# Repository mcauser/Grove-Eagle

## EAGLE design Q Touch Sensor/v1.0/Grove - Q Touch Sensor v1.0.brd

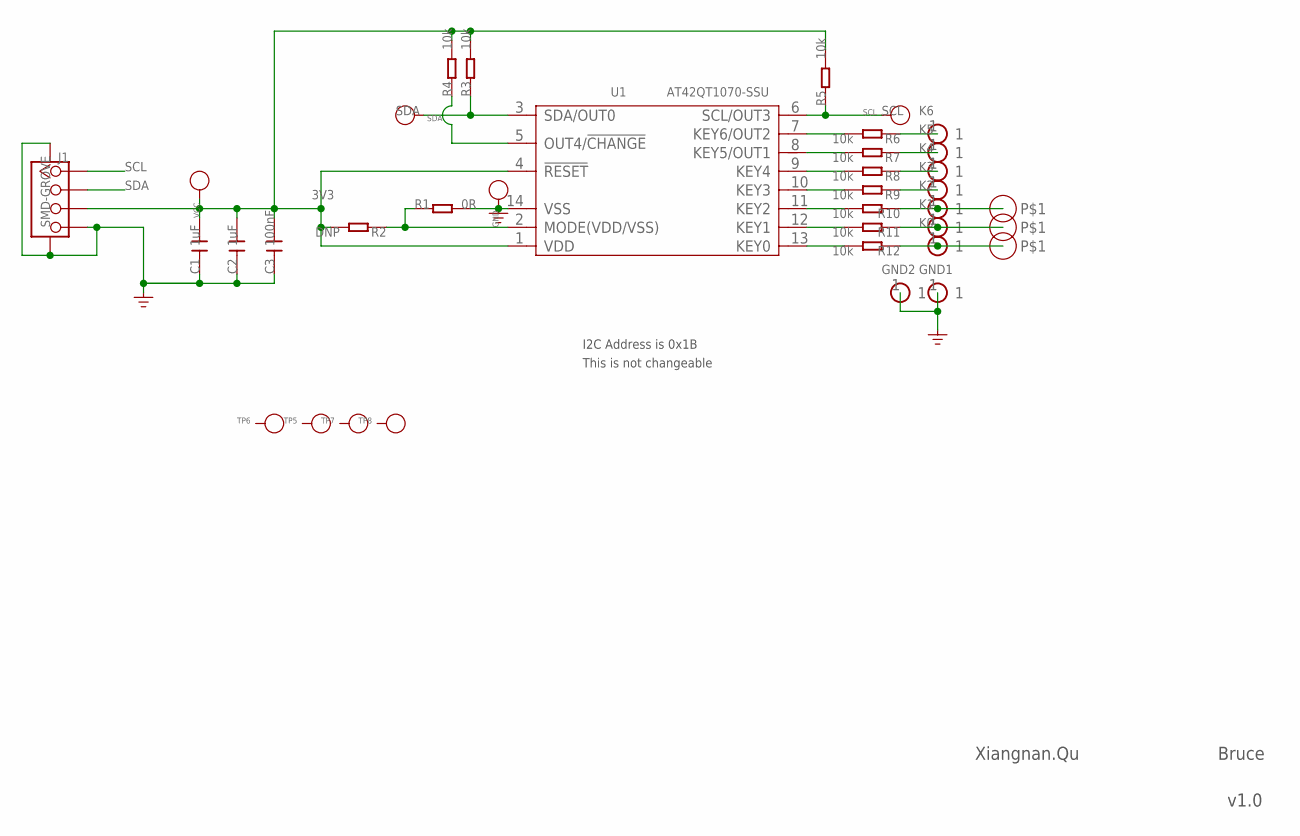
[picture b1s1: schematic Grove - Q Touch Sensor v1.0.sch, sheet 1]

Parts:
C1, C2: 1uF; C0603
C3: 100nF; C0603
GND: PAD-TEST-POINT'4545'; TP_4545
GND1, GND2: HEADER-1P-35; 1P-65/35MIL
J1: SMD-GROVE; 4P-SMD-2.0
K0, K1, K2, K3, K4, K5, K6: HEADER-1P-35; 1P-65/35MIL
P1, P2, P3: PAD-HOLE; 1P-D6MM
R1: 0R; R0603
R2: DNP; R0603
R3, R4, R5, R6, R7, R8, R9, R10, R11, R12: 10k; R0603
SCL: PAD-TEST-POINT'4545'; TP_4545
SDA: PAD-TEST-POINT'4545'; TP_4545
TP5, TP6, TP7, TP8: PAD-TEST-POINT'4545'; TP_4545
U1: AT42QT1070-SSU; SOIC14
VCC: PAD-TEST-POINT'4545'; TP_4545

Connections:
3V3: C1.2, C2.2, C3.2, J1.3, R2.2, R3.2, R4.2, R5.2, U1.1 (VDD), U1.4 (!RESET), VCC.T
GND: C1.1, C2.1, C3.1, GND.T, GND1.1, GND2.1, J1.4, J1.SS1, J1.SS2, R1.2, U1.14 (VSS)
unnamed: R1.1, R2.1, U1.2 (MODE(VDD/VSS))
unnamed: R6.2, U1.7 (KEY6/OUT2)
unnamed: K6.1, R6.1
unnamed: R7.2, U1.8 (KEY5/OUT1)
unnamed: R8.2, U1.9 (KEY4)
unnamed: R9.2, U1.10 (KEY3)
unnamed: R10.2, U1.11 (KEY2)
unnamed: R11.2, U1.12 (KEY1)
unnamed: R12.2, U1.13 (KEY0)
unnamed: R4.1, U1.5 (OUT4/!CHANGE)
unnamed: K5.1, R7.1
unnamed: K4.1, R8.1
unnamed: K3.1, R9.1
unnamed: K2.1, P1.1, R10.1
unnamed: K1.1, P2.1, R11.1
unnamed: K0.1, P3.1, R12.1
SCL: J1.1, R5.1, SCL.T, U1.6 (SCL/OUT3)
SDA: J1.2, R3.1, SDA.T, U1.3 (SDA/OUT0)

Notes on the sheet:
Xiangnan.Qu
Bruce
v1.0
I2C Address is 0x1B
This is not changeable

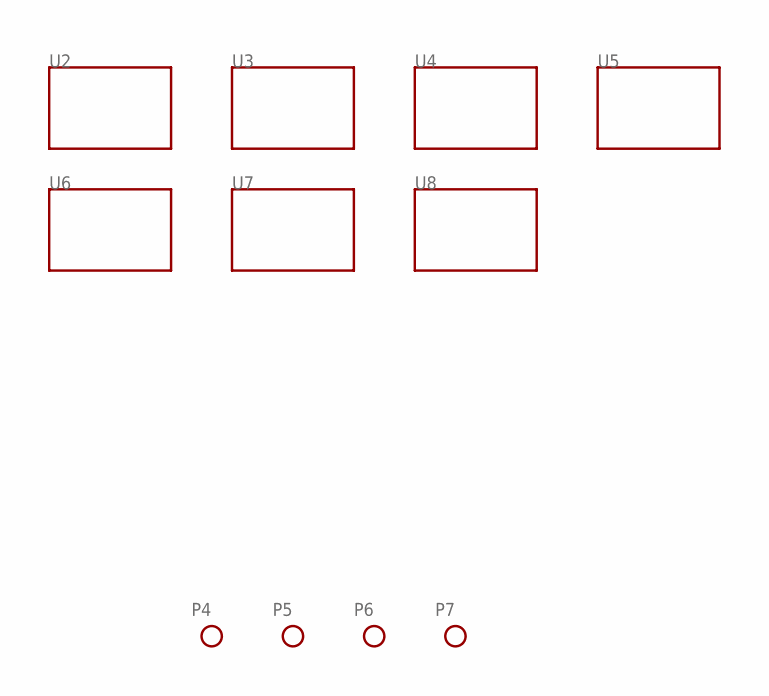
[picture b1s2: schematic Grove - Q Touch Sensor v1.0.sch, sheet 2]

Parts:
P4, P5, P6, P7: PAD-MARK; ROUND-MARK-1.0
U2, U3, U4, U5, U6, U7, U8: TWIG'2U'; GROVE-TEST-PLATFORM

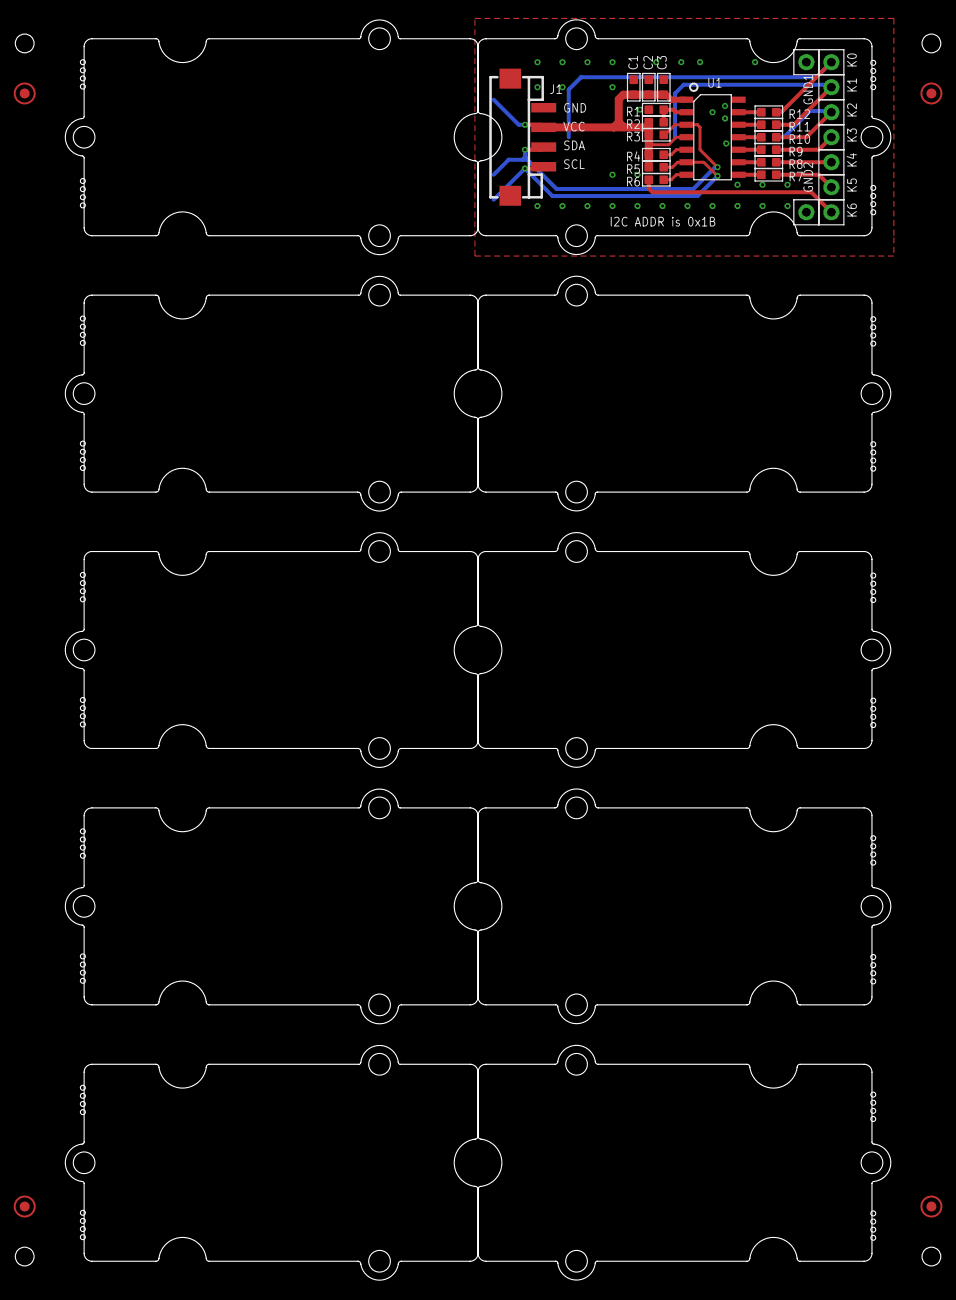
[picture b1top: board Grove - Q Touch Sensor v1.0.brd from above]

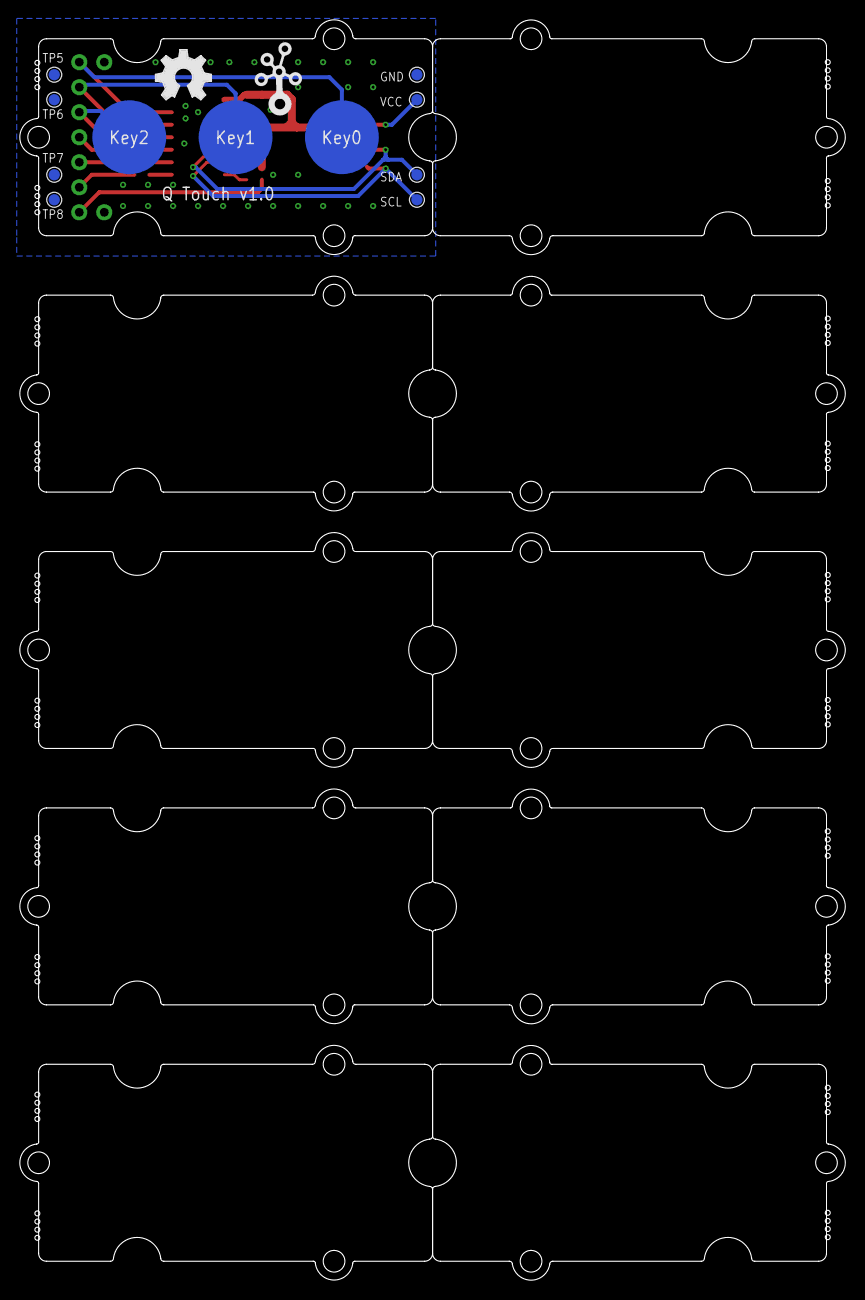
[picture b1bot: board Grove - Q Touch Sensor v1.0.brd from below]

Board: 2 copper layers, 83.8 x 128.0 mm, 53 parts (13 on the bottom side), 20 nets.

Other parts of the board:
U10, U11: GROVE-TEST-PLATFORM
U$5: GROVE-2CONNECTOR-SMD
U$6: OSHW_FILLX200_NOTEXT
U$7: TWIGLOGO

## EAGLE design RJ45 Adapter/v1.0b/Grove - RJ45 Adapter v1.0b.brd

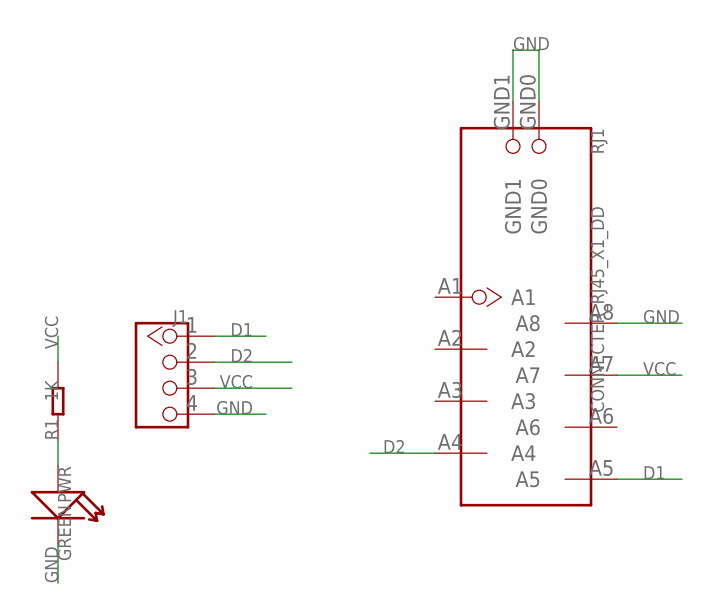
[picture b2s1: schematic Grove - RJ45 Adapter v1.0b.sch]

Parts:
J1: TWIG-4P-2.0-2.0; 4P-2.0
PWR: GREEN; LED-0603
R1: 1K; R0603
RJ1: CONNECTER_RJ45_X1_DD; CONNECTER_RJ45_X1

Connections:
D1: J1.1, RJ1.A5
D2: J1.2, RJ1.A4
GND: J1.4, PWR.-, RJ1.A8, RJ1.GND0, RJ1.GND1
unnamed: PWR.+, R1.1
VCC: J1.3, R1.2, RJ1.A7

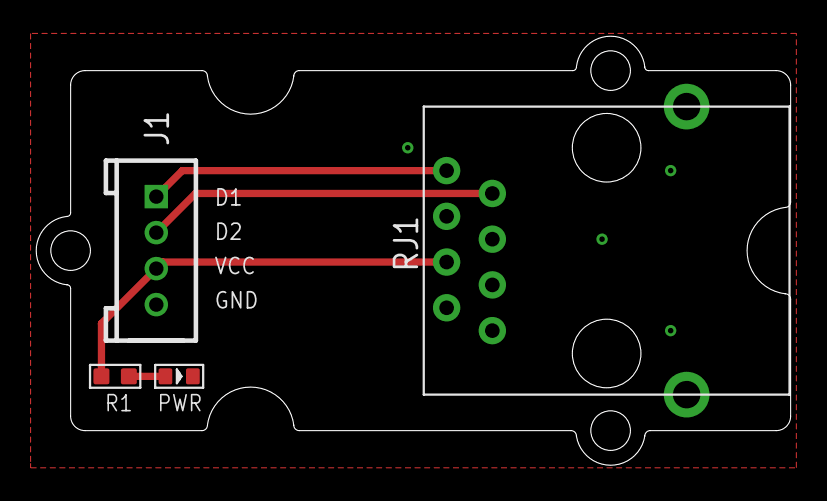
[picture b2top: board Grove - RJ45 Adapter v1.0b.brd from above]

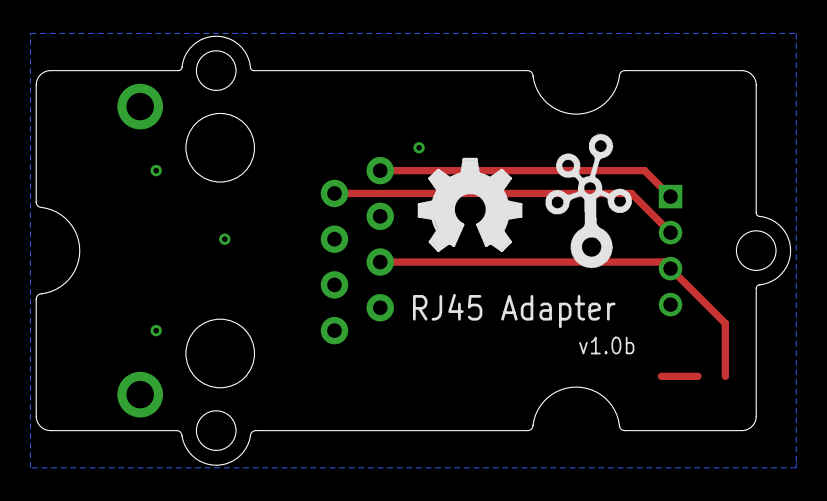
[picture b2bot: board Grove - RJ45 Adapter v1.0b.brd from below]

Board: 2 copper layers, 41.9 x 23.8 mm, 7 parts (2 on the bottom side), 5 nets.

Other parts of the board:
U$1: 2U-DIM-W/DRILL
U$2: OSHW_FILLX200_NOTEXT
U$3: TWIGLOGO

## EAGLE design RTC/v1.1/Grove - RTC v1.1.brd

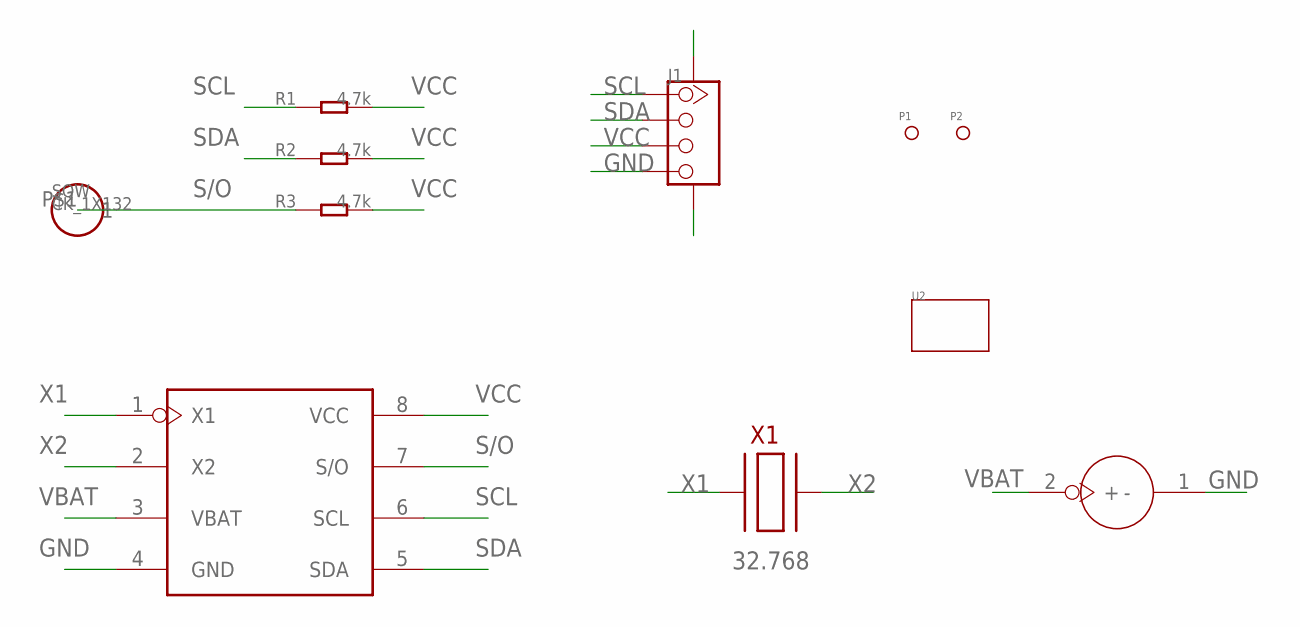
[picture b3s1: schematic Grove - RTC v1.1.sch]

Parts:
J1: TWIG-4P-2.0-SMD-FEMALE-REINFORCE'DD'; 4P-SMD-2.0
P1, P2: PAD-MARK; ROUND-MARK-1.0
R1, R2, R3: 4.7k; 0603
SQW: CK_1X132; CK_1X1
U1: DS1307; SO08
U2: TWIG-2U; 2U-DIM-W/-DRILL
U3: BATTERYBATTERY1225_SMT; BATTERY1225_SMT
X1: XTL_S

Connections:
GND: J1.4, J1.SS1, J1.SS2, U1.4 (GND), U3.1 (-)
S/O: R3.1, SQW.P$1, U1.7 (S/O)
SCL: J1.1, R1.1, U1.6 (SCL)
SDA: J1.2, R2.1, U1.5 (SDA)
VBAT: U1.3 (VBAT), U3.2 (+)
VCC: J1.3, R1.2, R2.2, R3.2, U1.8 (VCC)
X1: U1.1 (X1), X1.1
X2: U1.2 (X2), X1.2

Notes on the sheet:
32.768

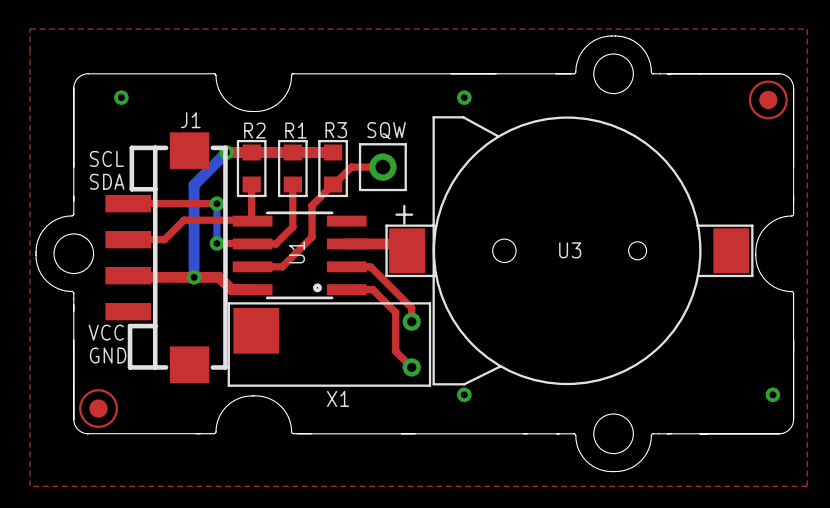
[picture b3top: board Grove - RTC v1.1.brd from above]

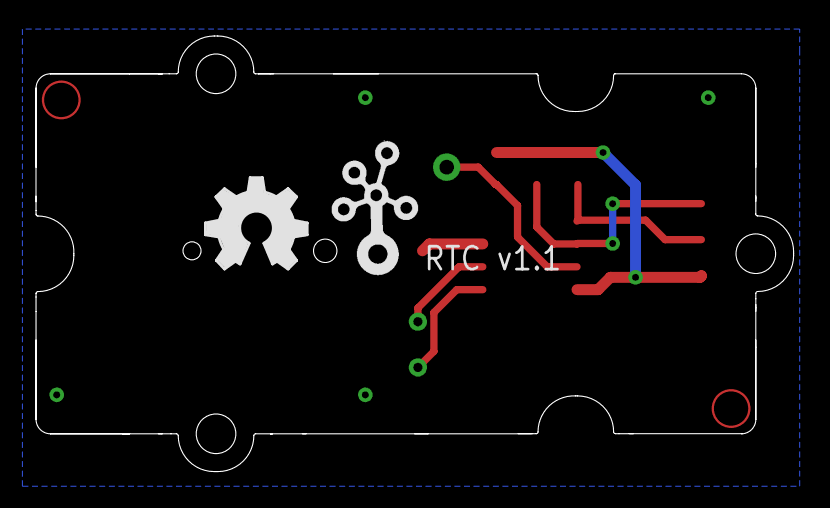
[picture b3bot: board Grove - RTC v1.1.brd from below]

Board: 2 copper layers, 42.1 x 24.2 mm, 13 parts (2 on the bottom side), 8 nets.

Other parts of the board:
U$1: OSHW_FILLX200_NOTEXT
U$3: TWIGLOGO

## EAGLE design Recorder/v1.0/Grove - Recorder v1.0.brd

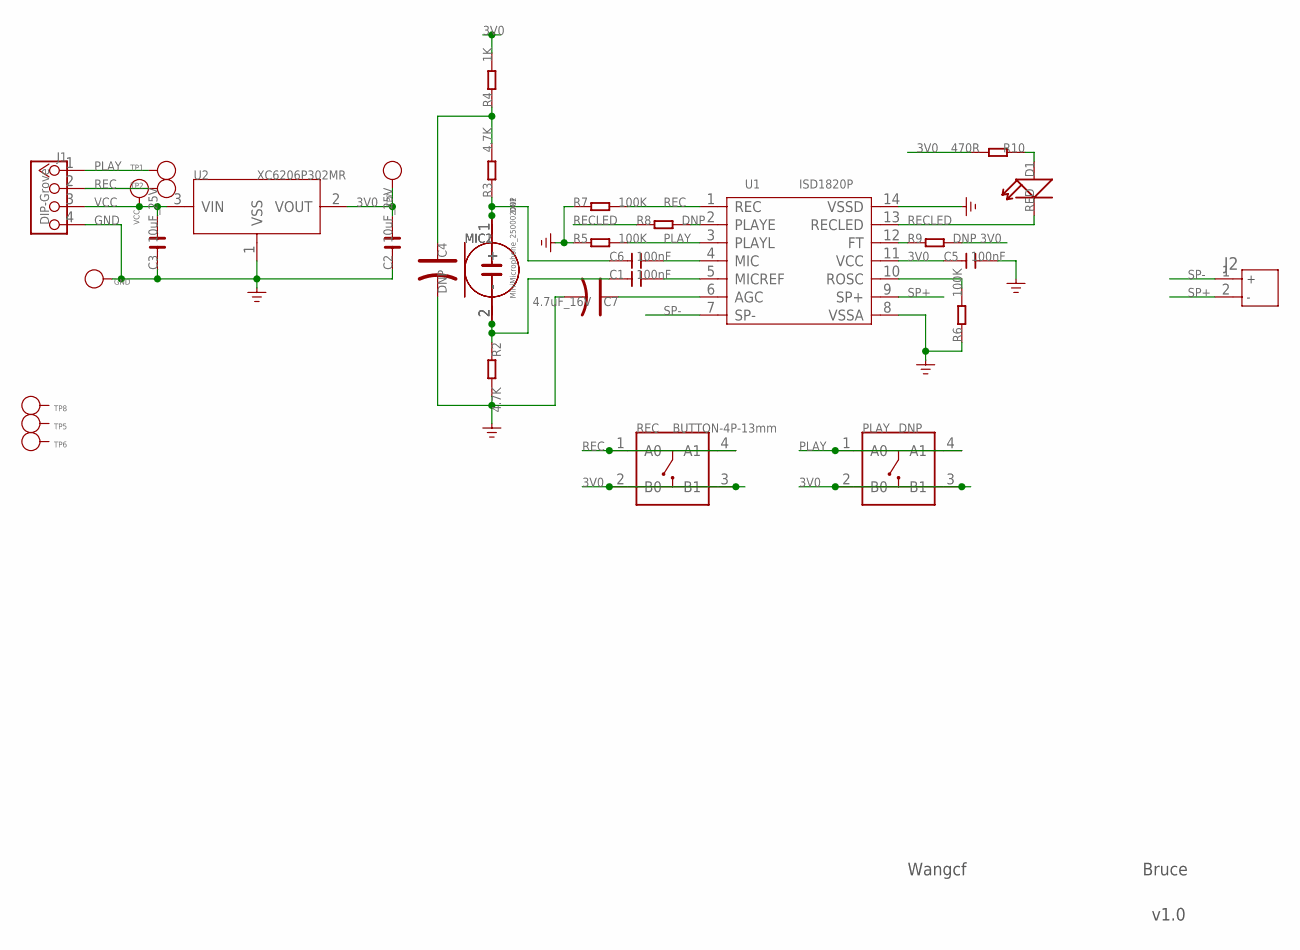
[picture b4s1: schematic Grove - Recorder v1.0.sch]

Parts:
C1, C5, C6: 100nF; C0603
C2, C3: 10uF_25V; C0805
C4: DNP; AVX-A
C7: 4.7uF_16V; AVX-A
D1: RED; LED-SIDE-VIEW-0603-RIGHT
GND: PAD-TEST-POINT'4545'; TP_4545
J1: DIP-Grove; 4P-2.0
J2: JACK-JST-2P-PW'2.0'; JST-2.0
MIC1: MiniMicrophone_250002001; 2P-D8.9MM
MIC2: DNP; 2P-D8.9MM
PLAY: DNP; 4P-6.0X6.0X5.0H
R2, R3: 4.7K; R0603
R4: 1K; R0603
R5, R6, R7: 100K; R0603
R8, R9: DNP; R0603
R10: 470R; R0603
REC: BUTTON-4P-13mm; 4P-6.0X6.0X5.0H
TP1, TP2, TP5, TP6, TP7, TP8: PAD-TEST-POINT'4545'; TP_4545
U1: ISD1820P; DIP14
U2: XC6206P302MR; SOT23
VCC: PAD-TEST-POINT'4545'; TP_4545

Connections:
3V0: C2.2, C5.1, PLAY.2 (B0), PLAY.3 (B1), R4.2, R9.2, R10.2, REC.2 (B0), REC.3 (B1), TP7.T, U1.11 (VCC), U2.2 (VOUT)
GND: C2.1, C3.1, C4.-, C5.2, C7.- (2), GND.T, J1.4, R2.2, R5.1, R6.1, R7.1, U1.8 (VSSA), U1.14 (VSSD), U2.1 (VSS)
unnamed: R8.2, U1.2 (PLAYE)
unnamed: D1.1 (+), R10.1
unnamed: C7.+ (1), U1.6 (AGC)
unnamed: C1.2, U1.5 (MICREF)
unnamed: C6.2, U1.4 (MIC)
unnamed: R9.1, U1.12 (FT)
unnamed: R6.2, U1.10 (ROSC)
unnamed: C4.+, R3.2, R4.1
unnamed: C6.1, MIC1.1 (+), MIC2.1 (+), R3.1
unnamed: C1.1, MIC1.2 (-), MIC2.2 (-), R2.1
PLAY: J1.1, PLAY.1 (A0), PLAY.4 (A1), R5.2, TP1.T, U1.3 (PLAYL)
REC: J1.2, R7.2, REC.1 (A0), REC.4 (A1), TP2.T, U1.1 (REC)
RECLED: D1.2 (-), R8.1, U1.13 (RECLED)
SP+: J2.2, U1.9 (SP+)
SP-: J2.1, U1.7 (SP-)
VCC: C3.2, J1.3, U2.3 (VIN), VCC.T

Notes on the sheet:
Wangcf
Bruce
v1.0

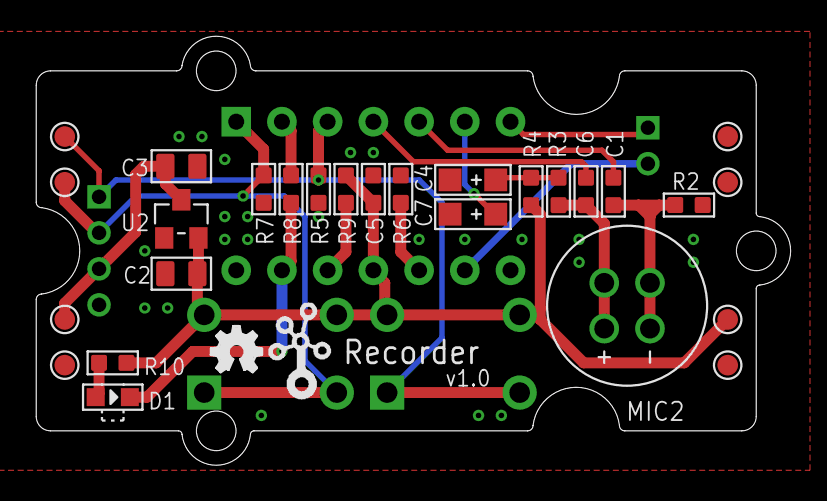
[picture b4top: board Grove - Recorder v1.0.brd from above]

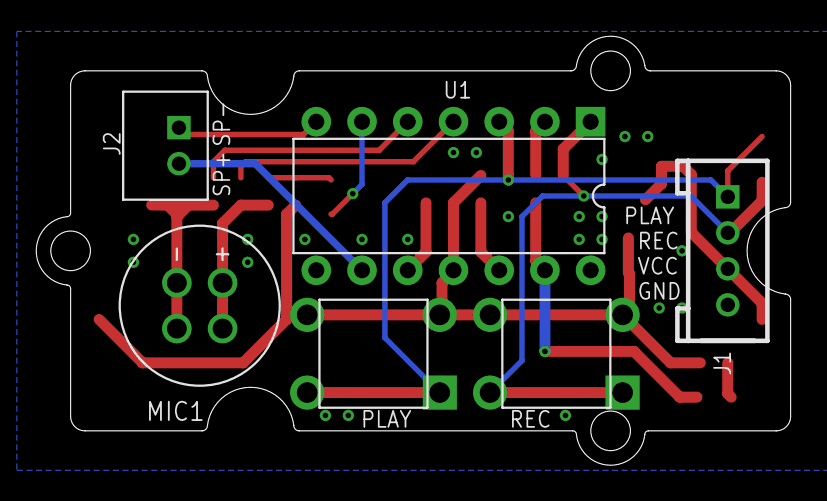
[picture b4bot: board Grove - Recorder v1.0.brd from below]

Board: 2 copper layers, 41.9 x 23.8 mm, 36 parts (6 on the bottom side), 18 nets.

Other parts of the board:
U$9: GROVE-2CONNECTOR
U$10: TWIGLOGO_SMALL
U$11: OSHW_FILLX100_NOTEXT

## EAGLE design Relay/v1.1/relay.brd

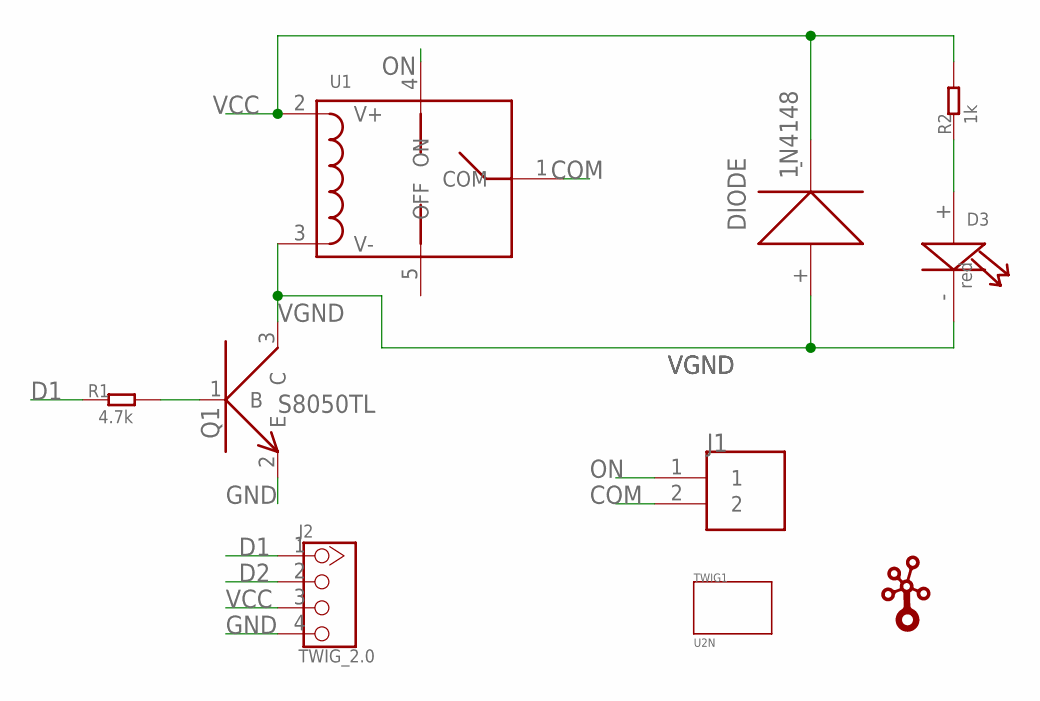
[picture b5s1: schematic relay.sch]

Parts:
D3: red; LED0805
DIODE: 1N4148; DIODE1206
J1: CON2
J2: TWIG_2.0; 2.0_1X4
Q1: NPN_9013; SOT23
R1: 4.7k; 0603
R2: 1k; 0603
TWIG1: U2N
U1: RELAY
U$1: TWIGLOGOTWIGLOGO_SMALL; TWIGLOGO_SMALL

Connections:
COM: J1.2, U1.1 (COM)
D1: J2.1, R1.1
D2: J2.2
GND: J2.4, Q1.2 (E)
unnamed: D3.+, R2.1
unnamed: Q1.1 (B), R1.2
ON: J1.1, U1.4 (ON)
VCC: DIODE.-, J2.3, R2.2, U1.2 (V+)
VGND: D3.-, DIODE.+, Q1.3 (C), U1.3 (V-)

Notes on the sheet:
S8050TL

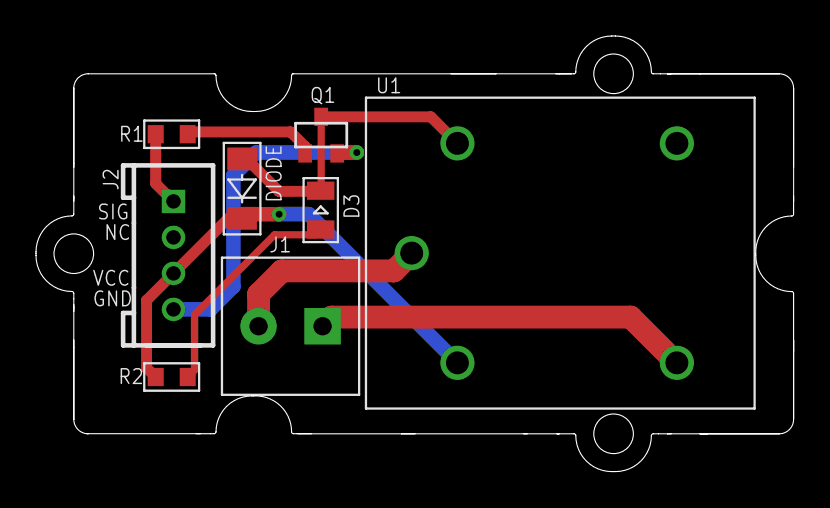
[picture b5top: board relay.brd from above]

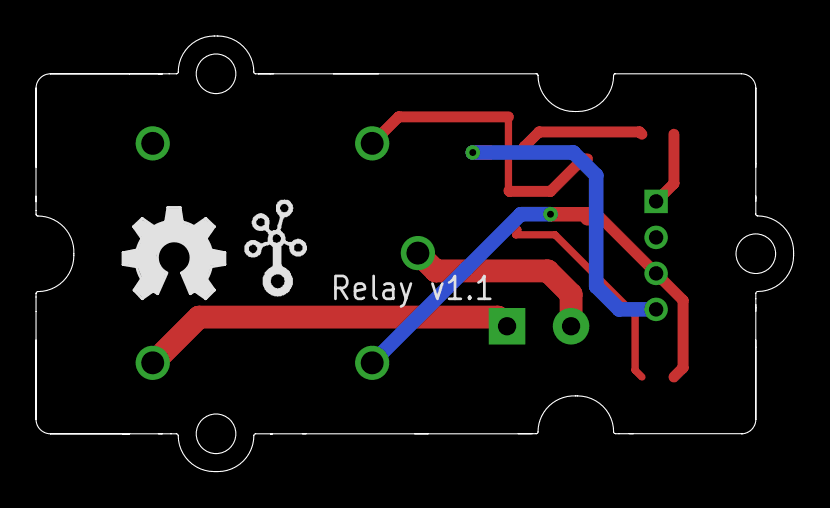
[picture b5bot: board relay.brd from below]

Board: 2 copper layers, 42.1 x 24.2 mm, 11 parts (2 on the bottom side), 8 nets.

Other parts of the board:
U$2: OSHW_FILLX200_NOTEXT

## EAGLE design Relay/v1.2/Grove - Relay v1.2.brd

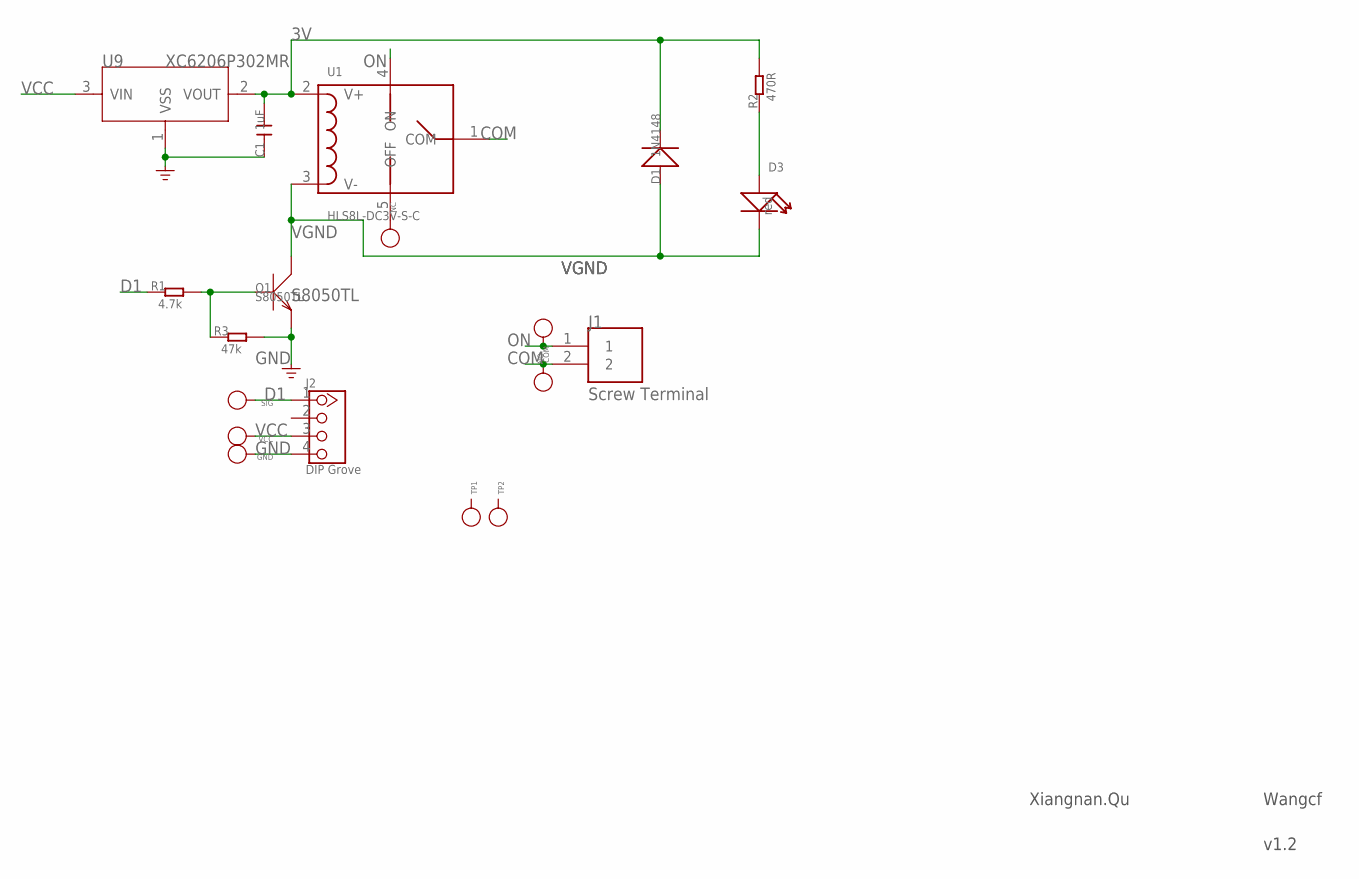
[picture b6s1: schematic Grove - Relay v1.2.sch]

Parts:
C1: 1uF; C0603
COM: PAD-TEST-POINT'4545'; TP_4545
D1: 1N4148; LL-34
D3: red; LED-0603
GND: PAD-TEST-POINT'4545'; TP_4545
J1: Screw Terminal; CON2
J2: DIP Grove; 2.0_1X4
NC: PAD-TEST-POINT'4545'; TP_4545
NO: PAD-TEST-POINT'4545'; TP_4545
Q1: S8050TL; SOT23
R1: 4.7k; R0603
R2: 470R; R0603
R3: 47k; R0603
SIG: PAD-TEST-POINT'4545'; TP_4545
TP1, TP2: PAD-TEST-POINT'4545'; TP_4545
U1: HLS8L-DC3V-S-C; RELAY
U9: XC6206P302MR; SOT23
VCC: PAD-TEST-POINT'4545'; TP_4545

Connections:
3V: C1.2, D1.C (-), R2.2, U1.2 (V+), U9.2 (VOUT)
COM: COM.T, J1.2, U1.1 (COM)
D1: J2.1, R1.1, SIG.T
GND: C1.1, GND.T, J2.4, Q1.2 (E), R3.2, U9.1 (VSS)
unnamed: D3.+, R2.1
unnamed: Q1.1 (B), R1.2, R3.1
unnamed: NC.T, U1.5 (OFF)
ON: J1.1, NO.T, U1.4 (ON)
VCC: J2.3, U9.3 (VIN), VCC.T
VGND: D1.A (+), D3.-, Q1.3 (C), U1.3 (V-)

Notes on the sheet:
S8050TL
Xiangnan.Qu
Wangcf
v1.2

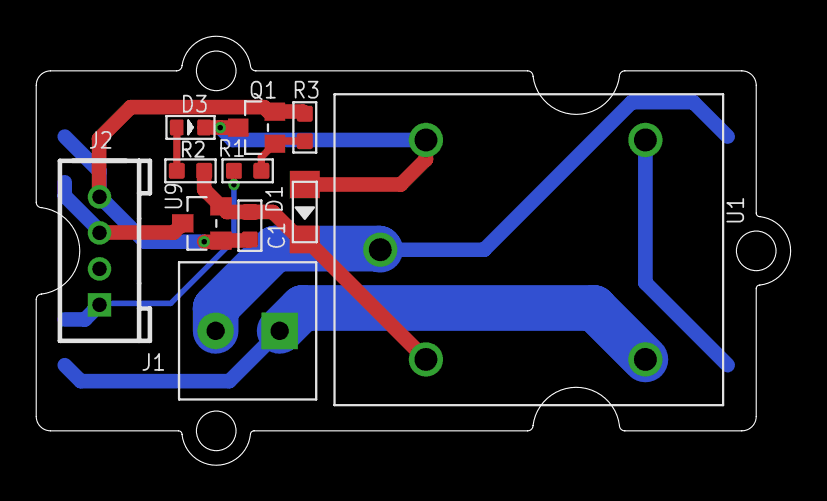
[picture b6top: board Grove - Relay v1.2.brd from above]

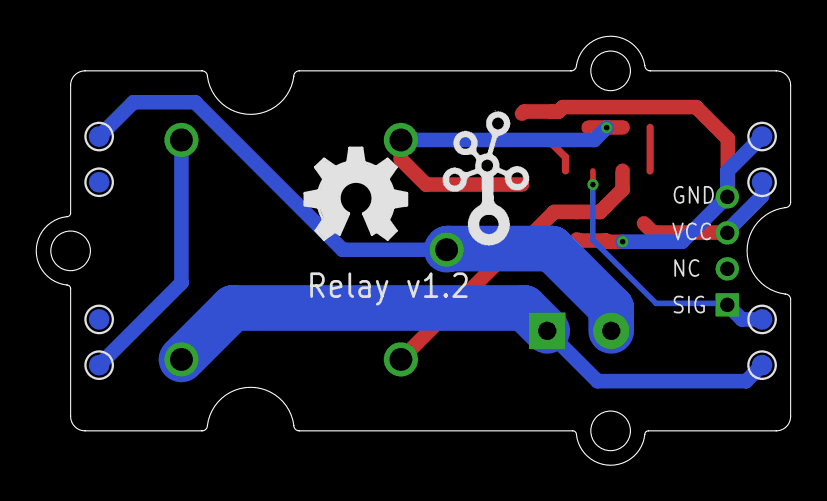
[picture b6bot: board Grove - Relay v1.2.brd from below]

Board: 2 copper layers, 41.9 x 23.8 mm, 22 parts (10 on the bottom side), 10 nets.

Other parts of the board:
U$2: OSHW_FILLX200_NOTEXT
U$3: GROVE-TEST-PLATFORM
U$5: TWIGLOGO

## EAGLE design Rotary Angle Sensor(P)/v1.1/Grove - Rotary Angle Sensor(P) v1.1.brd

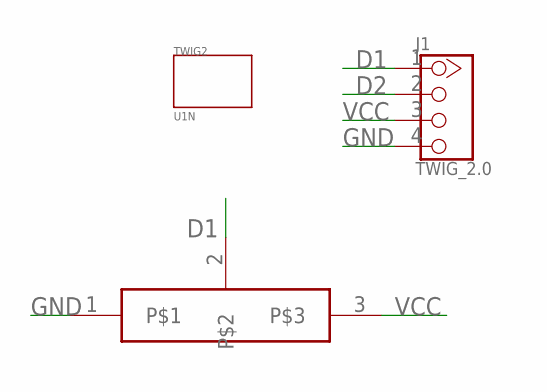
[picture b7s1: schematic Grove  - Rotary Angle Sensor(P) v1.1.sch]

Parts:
J1: TWIG_2.0; 2.0_1X4
TWIG2: U1N
U$1: ROTATION

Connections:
D1: J1.1, U$1.2
D2: J1.2
GND: J1.4, U$1.1
VCC: J1.3, U$1.3
